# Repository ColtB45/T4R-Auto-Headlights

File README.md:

# T4R-Auto-Headlights
Automatic Headlights for 5th Gen Toyota 4Runners

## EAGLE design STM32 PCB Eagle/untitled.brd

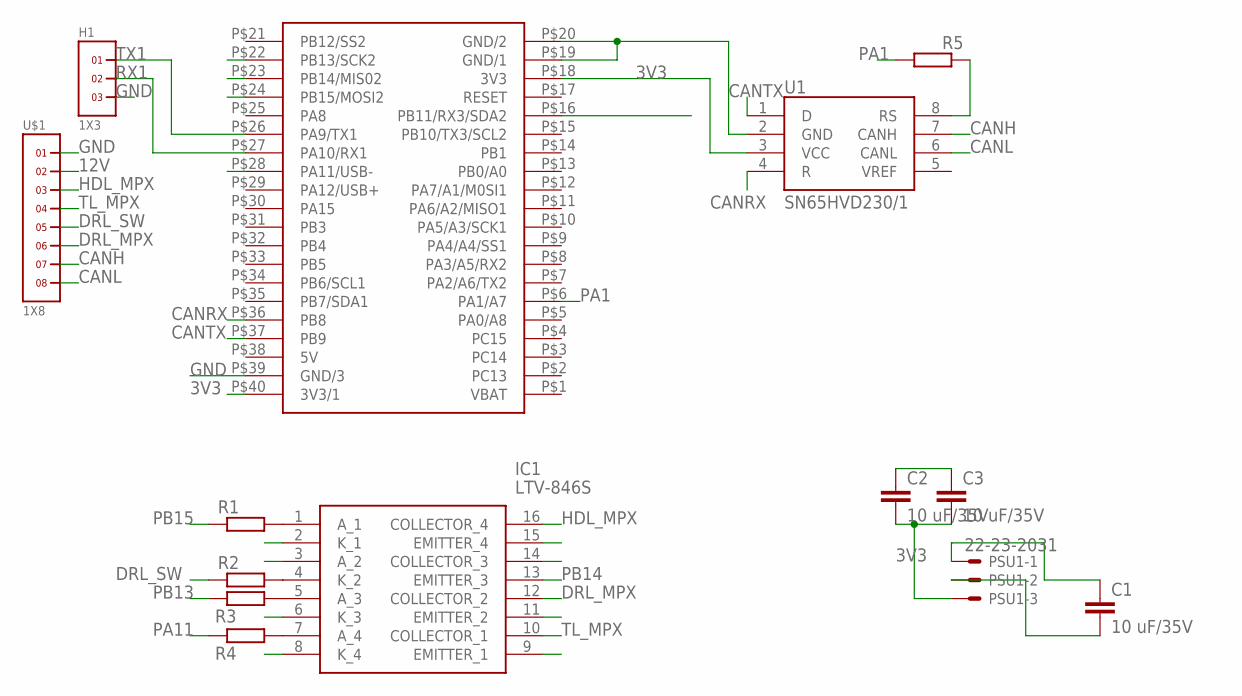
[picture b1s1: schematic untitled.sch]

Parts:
C1, C2, C3: 10 uF/35V; C1206
H1: 1X3
IC1: LTV-846S; SOP254P1016X460-16N
PSU1: 22-23-2031
R1, R3, R4: 47 ohm; R1206
R2: 1k ohm; R1206
R5: 47k ohm; R1206
STM32: BLUEPILL; 40-DIP-BLUE-PIL
U1: SN65HVD230/1; SO8
U$1: 1X8

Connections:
3V3: C2.2, C3.2, IC1.3 (A_2), IC1.14 (COLLECTOR_3), PSU1.3, STM32.P$18 (3V3), STM32.P$40 (3V3/1), U1.3 (VCC)
12V: C1.1, PSU1.1, U$1.2
CANH: U1.7 (CANH), U$1.7
CANL: U1.6 (CANL), U$1.8
CANRX: STM32.P$36 (PB8), U1.4 (R)
CANTX: STM32.P$37 (PB9), U1.1 (D)
DRL_MPX: IC1.12 (COLLECTOR_2), U$1.6
DRL_SW: R2.1, U$1.5
GND: C1.2, C2.1, C3.1, H1.3, IC1.2 (K_1), IC1.6 (K_3), IC1.8 (K_4), IC1.9 (EMITTER_1), IC1.11 (EMITTER_2), IC1.15 (EMITTER_4), PSU1.2, STM32.P$19 (GND/1), STM32.P$20 (GND/2), STM32.P$39 (GND/3), U1.2 (GND), U$1.1
HDL_MPX: IC1.16 (COLLECTOR_4), U$1.3
unnamed: IC1.1 (A_1), R1.2
unnamed: IC1.4 (K_2), R2.2
unnamed: IC1.5 (A_3), R3.2
unnamed: IC1.7 (A_4), R4.2
unnamed: R5.2, U1.8 (RS)
PA1: R5.1, STM32.P$6 (PA1/A7)
PA11: R4.1, STM32.P$28 (PA11/USB-)
PB11: STM32.P$16 (PB11/RX3/SDA2)
PB13: R3.1, STM32.P$22 (PB13/SCK2)
PB14: IC1.13 (EMITTER_3), STM32.P$23 (PB14/MIS02)
PB15: R1.1, STM32.P$24 (PB15/MOSI2)
RX1: H1.2, STM32.P$27 (PA10/RX1)
TL_MPX: IC1.10 (COLLECTOR_1), U$1.4
TX1: H1.1, STM32.P$26 (PA9/TX1)

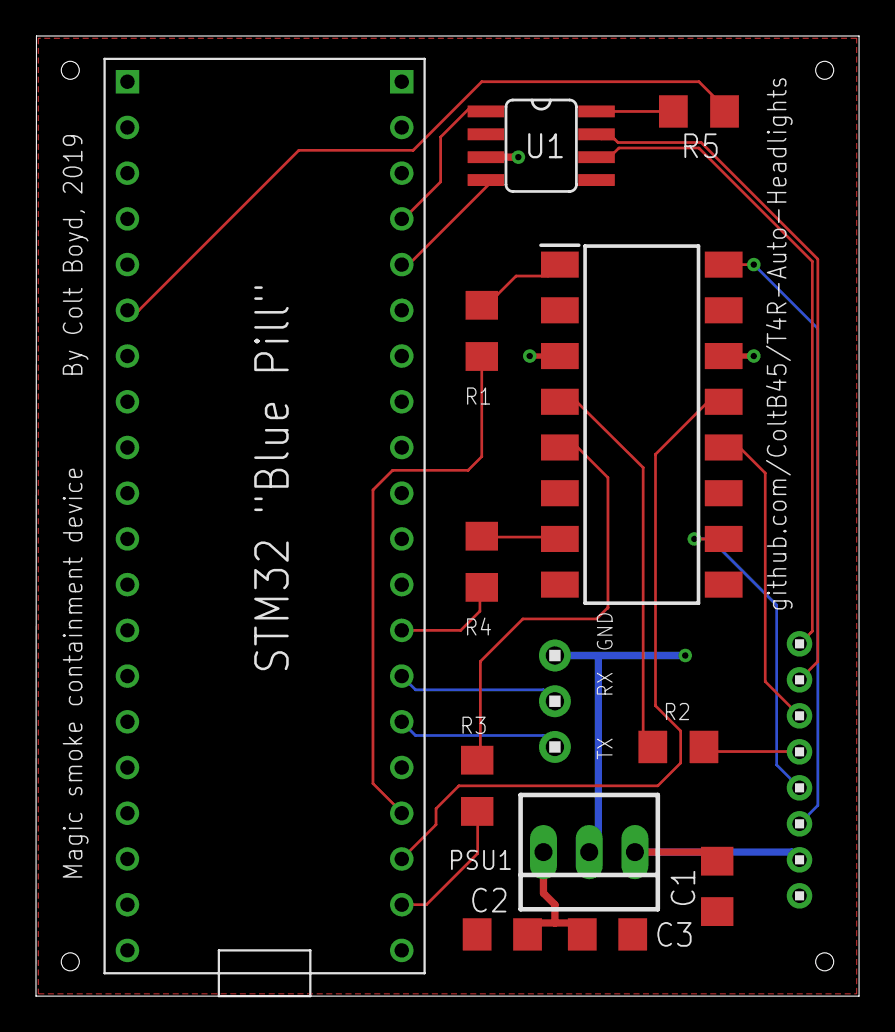
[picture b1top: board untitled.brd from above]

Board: 2 copper layers, 45.7 x 53.3 mm, 14 parts (0 on the bottom side), 23 nets.

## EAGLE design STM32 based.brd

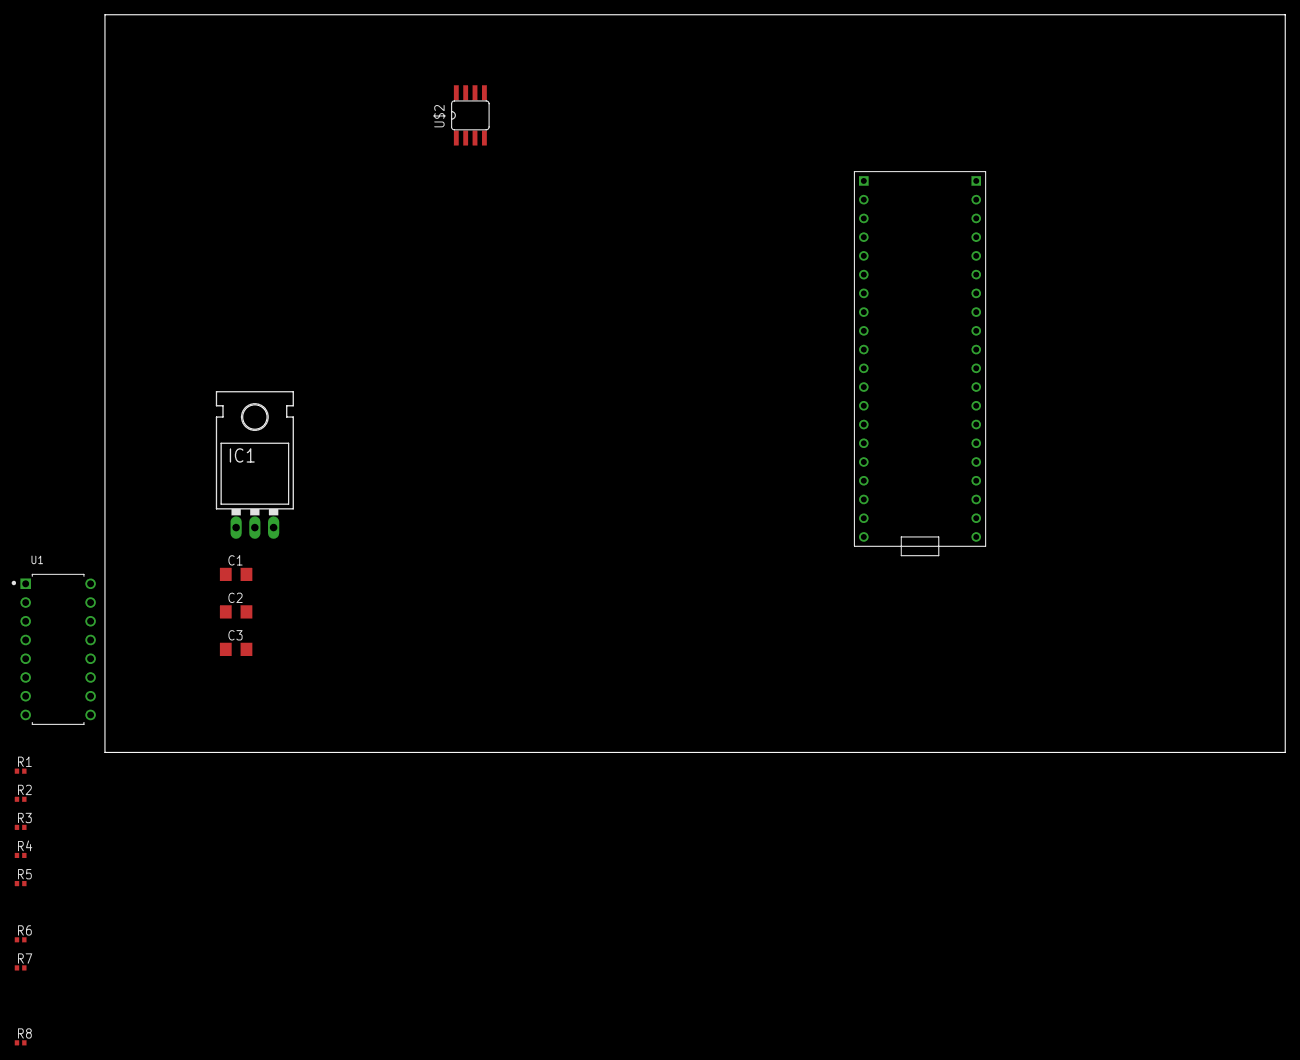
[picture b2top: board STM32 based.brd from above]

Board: 2 copper layers, 160.0 x 100.0 mm, 15 parts (0 on the bottom side), 18 nets, no tracks yet.

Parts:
C1, C2, C3: 10 uF/35V; C1206
IC1: TO220L1
R1, R2, R3, R4, R5, R7, R8: 1k ohm; R0402
R6: 47k ohm; R0402
U1: LTV-846; DIP880W50P254L2034H450Q16
U$1: BLUEPILL; 40-DIP-BLUE-PIL
U$2: SN65HVD230/1; SO8

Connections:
3V3: C2.2, C3.2, IC1.3, U1.3, U1.14, U$1.P$18, U$1.P$40, U$2.3
12V: C1.1, IC1.1
CANRX: U$1.P$36, U$2.4
CANTX: U$1.P$37, U$2.1
GND: C1.2, C2.1, C3.1, IC1.2, U1.2, U1.6, U1.8, U1.9, U1.11, U1.15, U$1.P$19, U$1.P$20, U$1.P$39, U$2.2
unnamed: R1.2, U1.1
unnamed: R2.2, U1.4
unnamed: R3.2, U1.5
unnamed: R4.2, U1.7
unnamed: R5.1, U1.16
unnamed: R6.1, U1.13
unnamed: R8.1, U1.10
unnamed: R7.1, U1.12
PA11: R4.1, U$1.P$28
PB11: U$1.P$16, U$2.8
PB13: R3.1, U$1.P$22
PB14: R6.2, U$1.P$23
PB15: R1.1, U$1.P$24

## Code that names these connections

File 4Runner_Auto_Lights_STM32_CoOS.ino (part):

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byte bitVar1 = 0;   // MSB to LSB, 7 = itsDark, 6 = talk, 5 = brightsOn, 4 = fogOn, 3 lightsOn, 2 turnLightsOnOff, 1 DRLlastStatus, 0 functionMode

//static bool functionMode      = 0;                    // 1 = CAN only, 0 = Switch + CAN
static bool debug             = 1;                      // 0 = release, 1 = debug on, prints debug info out over PA9
static bool superBrights      = 0;                      // 0 =off, 1 = on, allows the fog lights to operate while brights are on
static word nitLvlOn          = 350;                    // level at which to turn on lights   (0 bright, to 65,535 dark)
static word nitLvlOff         = nitLvlOn - 60;          // level at which to turn off lights  (0 bright, to 65,535 dark)
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        case 0x758: {

            // If DRL switch is deteched high, change function mode to Switch + CAN
            if (bitRead(bitVar1, 0) && digitalRead(PB14)) {
              bitWrite(bitVar1, 0, 0);
              if (debug) {
                Serial1.println("Changing function mode to 0, Switch + CAN");
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            // stuff here for reading switches status
            if (r_msg->Data[0] == 0x40 && r_msg->Data[1] == 0x05 && r_msg->Data[2] == 0x61 && r_msg->Data[3] == 0xA7) {
              //    if (((r_msg->Data[4] >> 5) & 1)){
              if ((bitRead(bitVar1, 0) && bitRead(r_msg->Data[4], 2)) || (bitRead(bitVar1, 0) == 0 && digitalRead(PB14))) {
                if (debug) {
                  Serial1.println("Auto Lights on");
                }
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    if (bitRead(bitVar1, 6)) {

      // wakeup CAN driver
      digitalWrite(PA1, LOW);

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      CoTickDelay((sendFreq * clockCor) / 2);
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        }
        // turn on taillights
        digitalWrite(PA11, HIGH);
        // turn on headlights
        digitalWrite(PB15, HIGH);
        // turn off DRLs
        digitalWrite(PB13, LOW);
      } else {
        bitWrite(bitVar1, 3, 0);
        if (bitRead(bitVar1, 0) || superBrights) {
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        }
        // turn off taillights
        digitalWrite(PA11, LOW);
        // turn off headlights
        digitalWrite(PB15, LOW);
        // turn on DRLs
        digitalWrite(PB13, HIGH);
      }
    } else {
      // turn off taillights
      digitalWrite(PA11, LOW);
      // turn off headlights
      digitalWrite(PB15, LOW);
      // turn off DRLs
      digitalWrite(PB13, LOW);
      // put can driver to sleep
      digitalWrite(PA1, HIGH);
    }
    CoTickDelay((sendFreq * clockCor) / 2);
  }
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
  // SN65HVD230 TX Sleep
  // drive high to put CAN driver to sleep, drive low to allow transmitting
  pinMode(PA1, OUTPUT);

  // optocoupler CH1
  // drive headlights to BCM status
  pinMode(PB15, OUTPUT);

  // optocoupler CH2
  // detect DRL from switch status
  pinMode(PB14, INPUT_PULLDOWN);
  // If DRL switch is deteched high, change function mode to Switch + CAN
  if (digitalRead(PB14)) {
    bitWrite(bitVar1, 0, 0);
  } else {
    bitWrite(bitVar1, 0, 1);
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
  // optocoupler CH3
  // drive DRL to BCM status
  pinMode(PB13, OUTPUT);

  // optocoupler CH4
  // drive tailights to BCM status
  pinMode(PA11, OUTPUT);

  delay(2000 * clockCor);

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
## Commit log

2019-02-20 Rename 4Runner_Auto_Lights_STM32.ino to 4Runner_Auto_Lights_STM324Runner_Auto_Lights_STM32_CoOS.ino
2019-02-20 Rename 4Runner_Auto_Lights_STM324Runner_Auto_Lights_STM32_CoOS.ino to 4Runner_Auto_Lights_STM32_CoOS.ino
2019-02-21 Control lights electrically
    Added the ability to control the lights via electrical connections between the BCM/MPX & driver switch.
2019-02-24 Changed functionMode to auto detect
2019-02-27 Added sleep functionality for the SN65HVD230
2019-03-01 schematic for STM32 based
2019-03-03 Added debug support and disable Serial1(PA9/10) when not in debug
2019-03-03 Minor format cleanup
2019-03-03 Added serial debug hdr and minor rerouting
2019-03-03 Added required Eagle libraries
2019-03-04 Alterations to keep MPX resistance below 200 ohms
    The MPX only allows a resistance of < 250 ohms. I've made the following alterations to keep the LTV-846 resistance to MPX ~200 ohms. The resistors between the LTV-846 and the MPX were there only to r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
    Removing these resistors should have no detrimental impact.
2019-03-07 This is the version sent to printing.
2019-03-07 test
2019-03-07 Added gerber files
2019-03-07 Changed PIN used for CAN sleep to match PCB
